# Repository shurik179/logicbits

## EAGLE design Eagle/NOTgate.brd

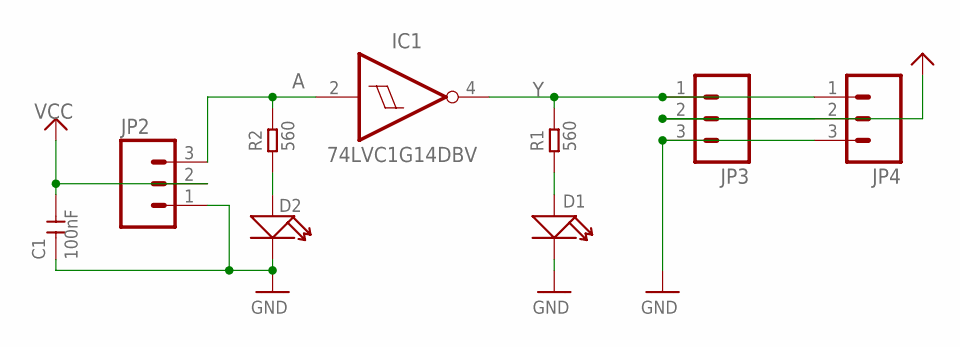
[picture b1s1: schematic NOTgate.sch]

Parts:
C1: 100nF; 0603
D1, D2: SMD-LED-0805; LED-0805
IC1: 74LVC1G14DBV; SOT23-5
JP2, JP3, JP4: SPARKFUN_M031SMD-RA-MALE; SPARKFUN_1X03-SMD-MALE
R1, R2: 560; 0603

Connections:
A: IC1.2 (I), JP2.3, R2.2
GND: C1.1, D1.-, D2.-, IC1.3 (GND), JP2.1, JP3.3, JP4.3
unnamed: D2.+, R2.1
unnamed: D1.+, R1.1
VCC: C1.2, IC1.5 (VCC), JP2.2, JP3.2, JP4.2
Y: IC1.4 (O), JP3.1, JP4.1, R1.2

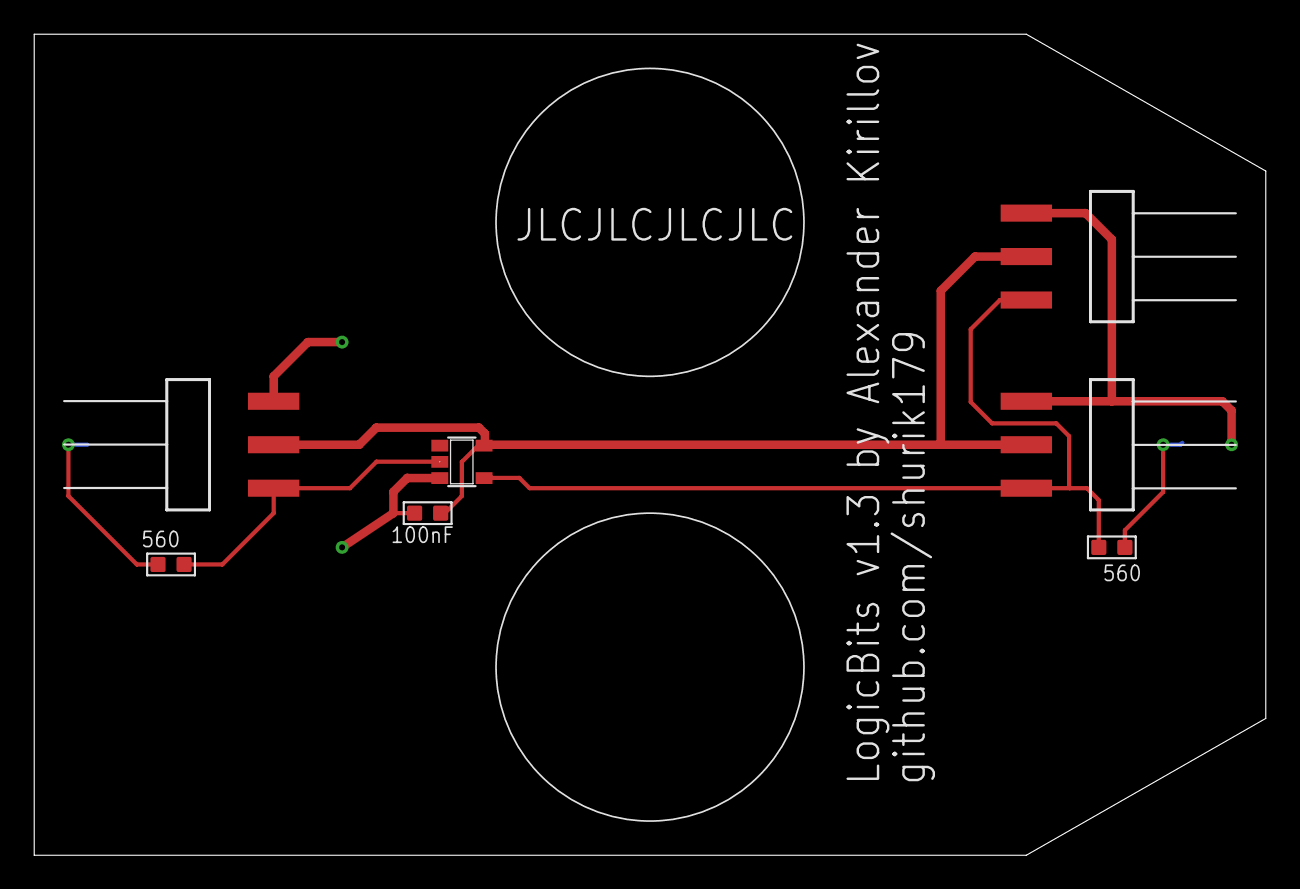
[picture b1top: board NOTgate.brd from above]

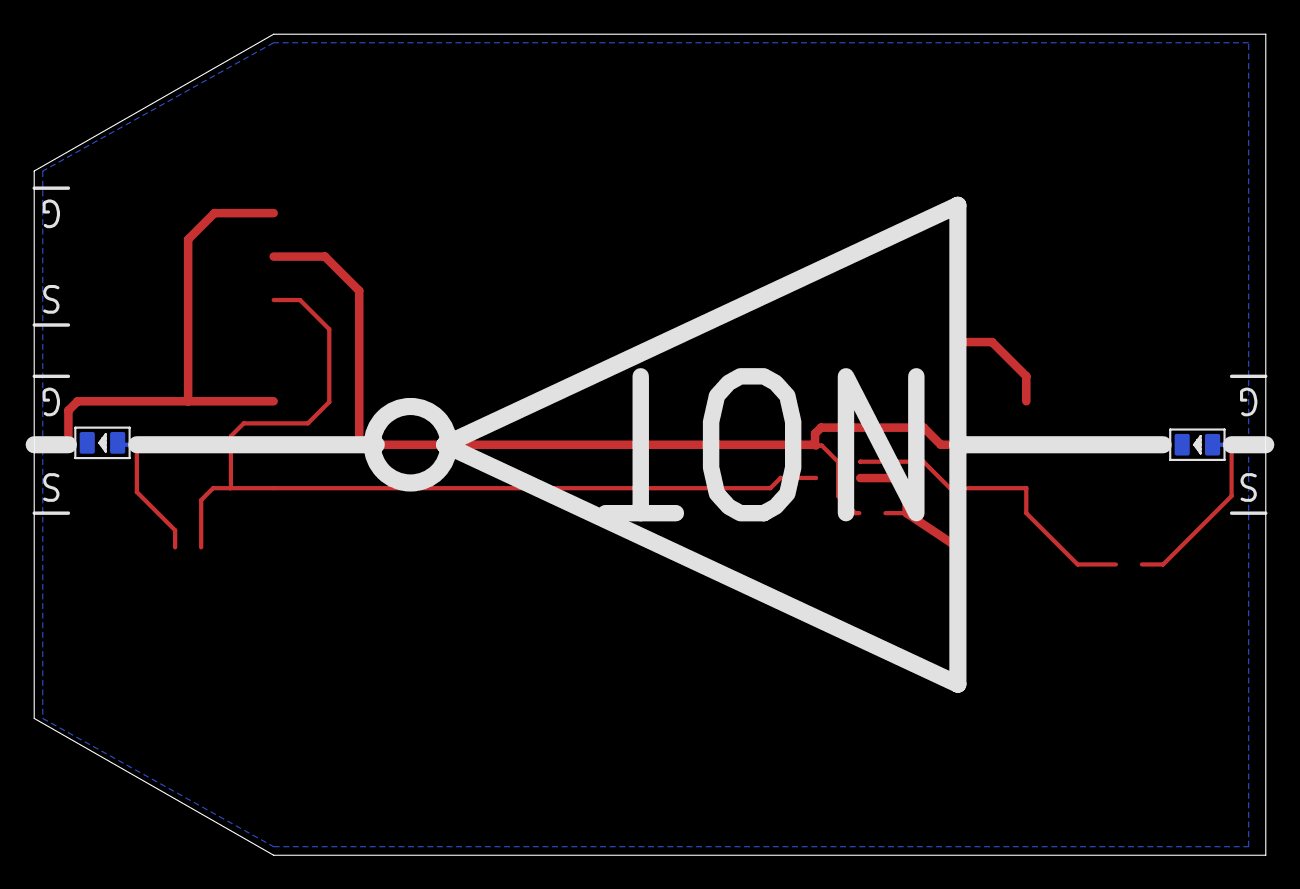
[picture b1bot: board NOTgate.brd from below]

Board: 2 copper layers, 72.0 x 48.0 mm, 9 parts (2 on the bottom side), 6 nets.

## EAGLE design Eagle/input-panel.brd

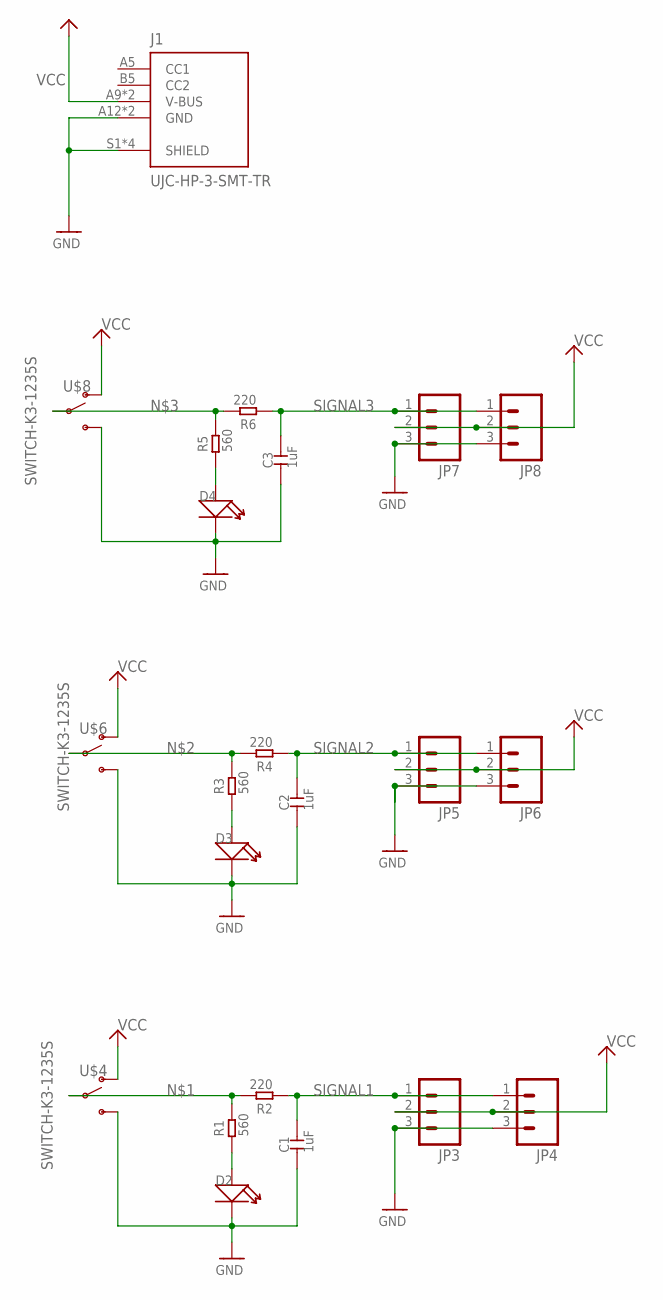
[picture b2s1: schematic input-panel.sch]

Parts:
C1, C2, C3: 1uF; 0603
D2, D3, D4: SMD-LED-0805; LED-0805
J1: UJC-HP-3-SMT-TR; CUI_UJC-HP-3-SMT-TR
JP3, JP4, JP5, JP6, JP7, JP8: SPARKFUN_M031SMD-RA-MALE; SPARKFUN_1X03-SMD-MALE
R1, R3, R5: 560; 0603
R2, R4, R6: 220; 0603
U$4, U$6, U$8: SWITCH-K3-1235S

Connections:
GND: C1.1, C2.1, C3.1, D2.-, D3.-, D4.-, J1.A12 (GND), J1.B12 (GND), J1.S1 (SHIELD), J1.S2 (SHIELD), J1.S3 (SHIELD), J1.S4 (SHIELD), JP3.3, JP4.3, JP5.3, JP6.3, JP7.3, JP8.3, U$4.P$3 (S), U$6.P$3 (S), U$8.P$3 (S)
unnamed: R1.2, R2.2, U$4.P$2
unnamed: R3.2, R4.2, U$6.P$2
unnamed: R5.2, R6.2, U$8.P$2
unnamed: D3.+, R3.1
unnamed: D2.+, R1.1
unnamed: D4.+, R5.1
SIGNAL1: C1.2, JP3.1, JP4.1, R2.1
SIGNAL2: C2.2, JP5.1, JP6.1, R4.1
SIGNAL3: C3.2, JP7.1, JP8.1, R6.1
VCC: J1.A9 (V-BUS), J1.B9 (V-BUS), JP3.2, JP4.2, JP5.2, JP6.2, JP7.2, JP8.2, U$4.P$1 (O), U$6.P$1 (O), U$8.P$1 (O)

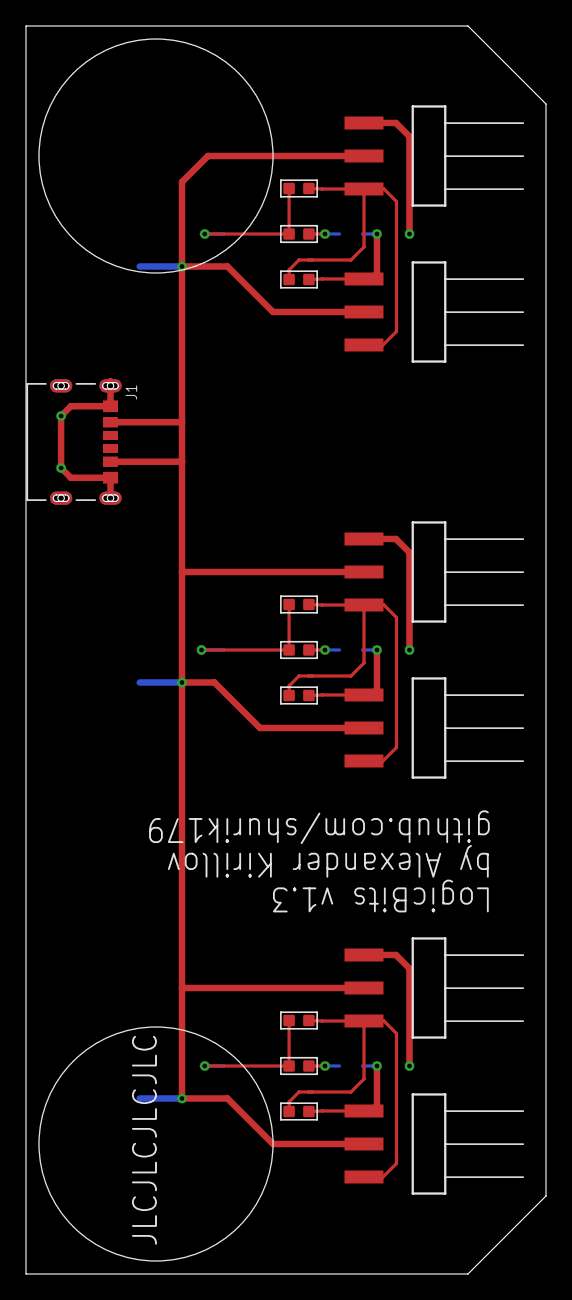
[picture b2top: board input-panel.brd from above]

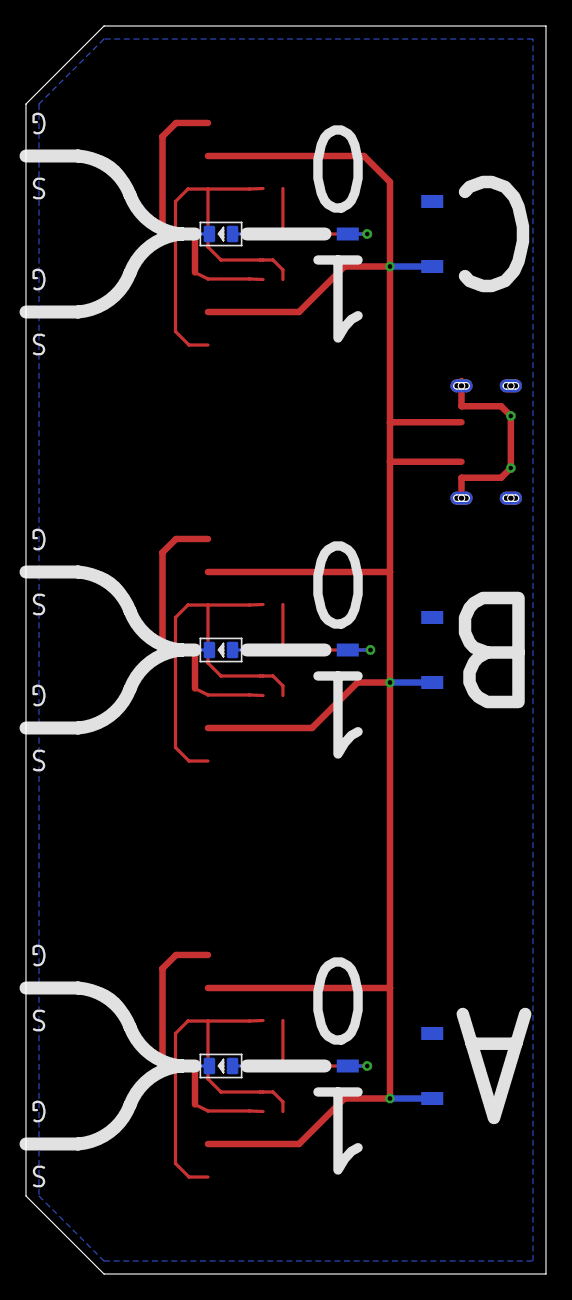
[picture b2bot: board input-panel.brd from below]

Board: 2 copper layers, 40.0 x 96.0 mm, 22 parts (6 on the bottom side), 11 nets.

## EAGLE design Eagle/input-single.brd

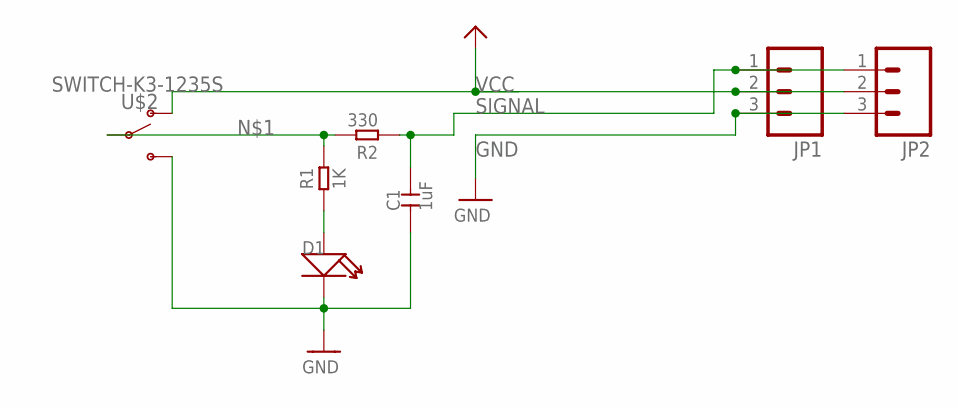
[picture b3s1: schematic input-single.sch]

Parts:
C1: 1uF; 0603
D1: SMD-LED-0805; LED-0805
JP1, JP2: SPARKFUN-CONNECTORS_M03SMD_RA_MALE; SPARKFUN-CONNECTORS_1X03_SMD_RA_MALE
R1: 1K; 0603
R2: 330; 0603
U$2: SWITCH-K3-1235S

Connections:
GND: C1.1, D1.-, JP1.3, JP2.3, U$2.P$3 (S)
unnamed: D1.+, R1.1, R1.2, R2.2, U$2.P$2
SIGNAL: C1.2, JP1.1, JP2.1, R2.1
VCC: JP1.2, JP2.2, U$2.P$1 (O)

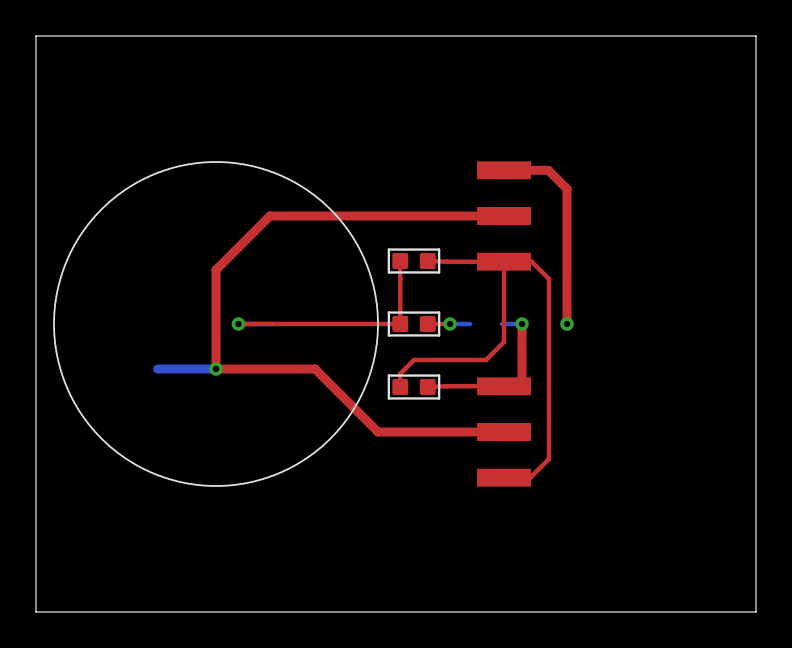
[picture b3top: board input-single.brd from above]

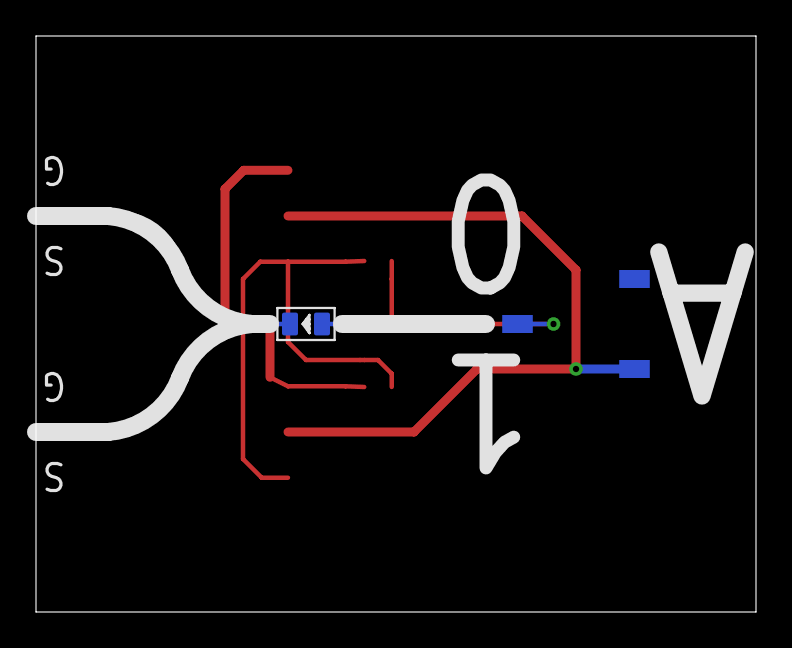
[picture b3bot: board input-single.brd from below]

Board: 2 copper layers, 40.0 x 32.0 mm, 7 parts (2 on the bottom side), 4 nets.
